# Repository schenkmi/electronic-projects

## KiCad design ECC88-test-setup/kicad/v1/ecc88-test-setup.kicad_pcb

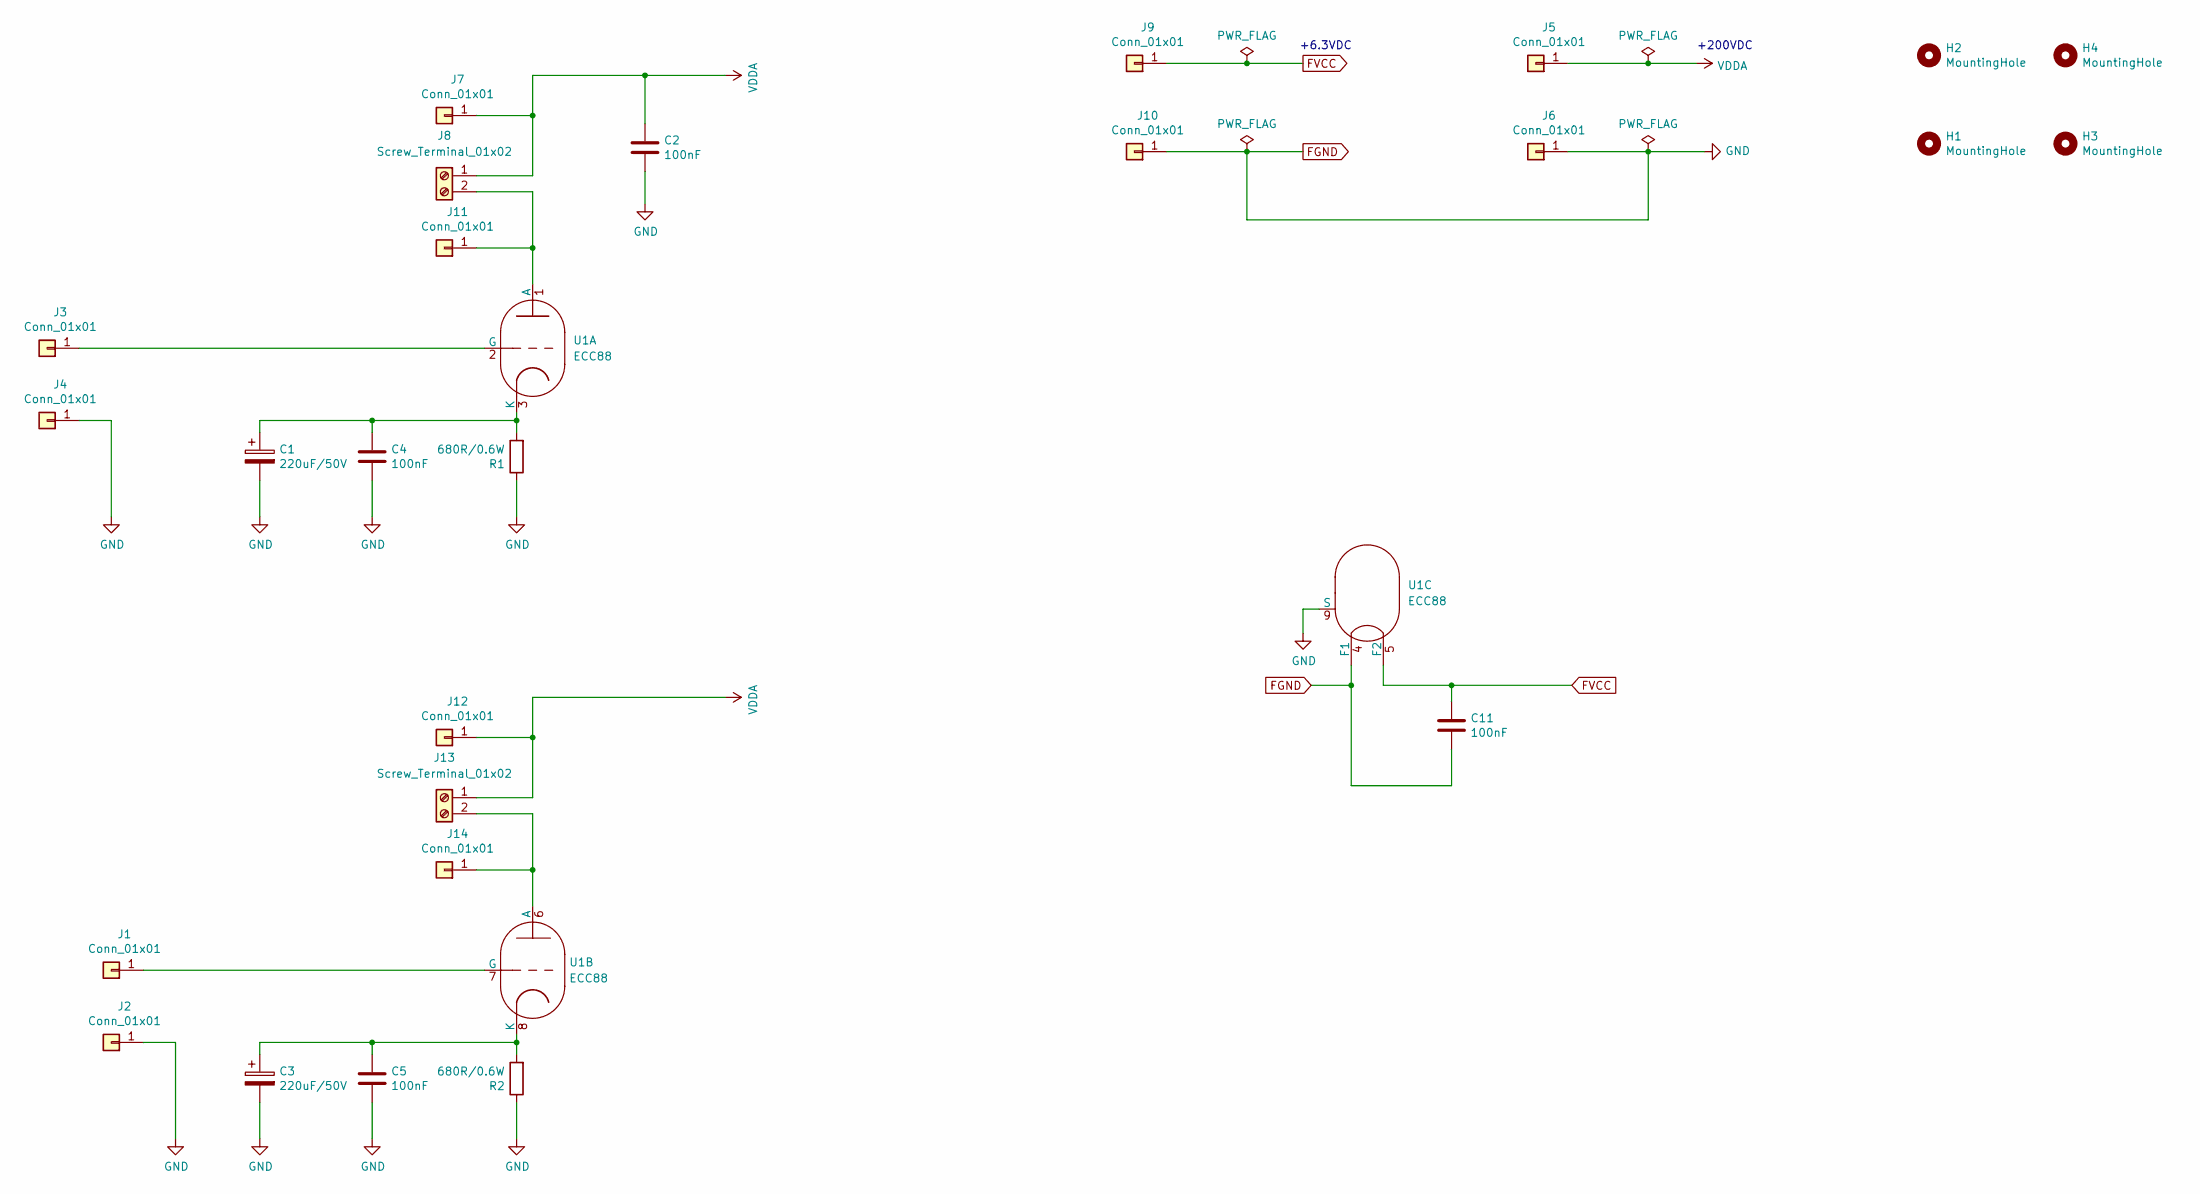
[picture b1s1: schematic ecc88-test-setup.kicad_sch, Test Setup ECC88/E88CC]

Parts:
C1, C3: 220uF/50V; CP_Radial_D8.0mm_P3.50mm
C2: 100nF; C_Rect_L16.5mm_W5.0mm_P15.00mm_MKT
C4, C5, C11: 100nF; C_Rect_L7.2mm_W2.5mm_P5.00mm_FKS2_FKP2_MKS2_MKP2
H1, H2, H3, H4: MountingHole; MountingHole_3.2mm_M3
J1, J2, J3, J4, J7, J11, J12, J14: Conn_01x01; Pin_D1.0mm_L10.0mm
J5, J6, J9, J10: Conn_01x01; Pin_D1.3mm_L11.0mm
J8, J13: Screw_Terminal_01x02; TerminalBlock_RND_205-00012_1x02_P5.00mm_Horizontal
R1, R2: 680R/0.6W; R_Axial_DIN0207_L6.3mm_D2.5mm_P10.16mm_Horizontal
U1: ECC88; socket_gzc9-b

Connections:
FGND: C1.2, C2.2, C3.2, C4.2, C5.2, C11.2, J2.1, J4.1, J6.1, J10.1, R1.1, R2.1, U1.4 (F1), U1.9 (S)
FVCC: C11.1, J9.1, U1.5 (F2)
unnamed: C3.1, C5.1, R2.2, U1.8 (K)
unnamed: J1.1, U1.7 (G)
unnamed: J3.1, U1.2 (G)
unnamed: J13.2, J14.1, U1.6 (A)
unnamed: J8.2, J11.1, U1.1 (A)
unnamed: C1.1, C4.1, R1.2, U1.3 (K)
VDDA: C2.1, J5.1, J7.1, J8.1, J12.1, J13.1

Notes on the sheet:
+6.3VDC
+200VDC

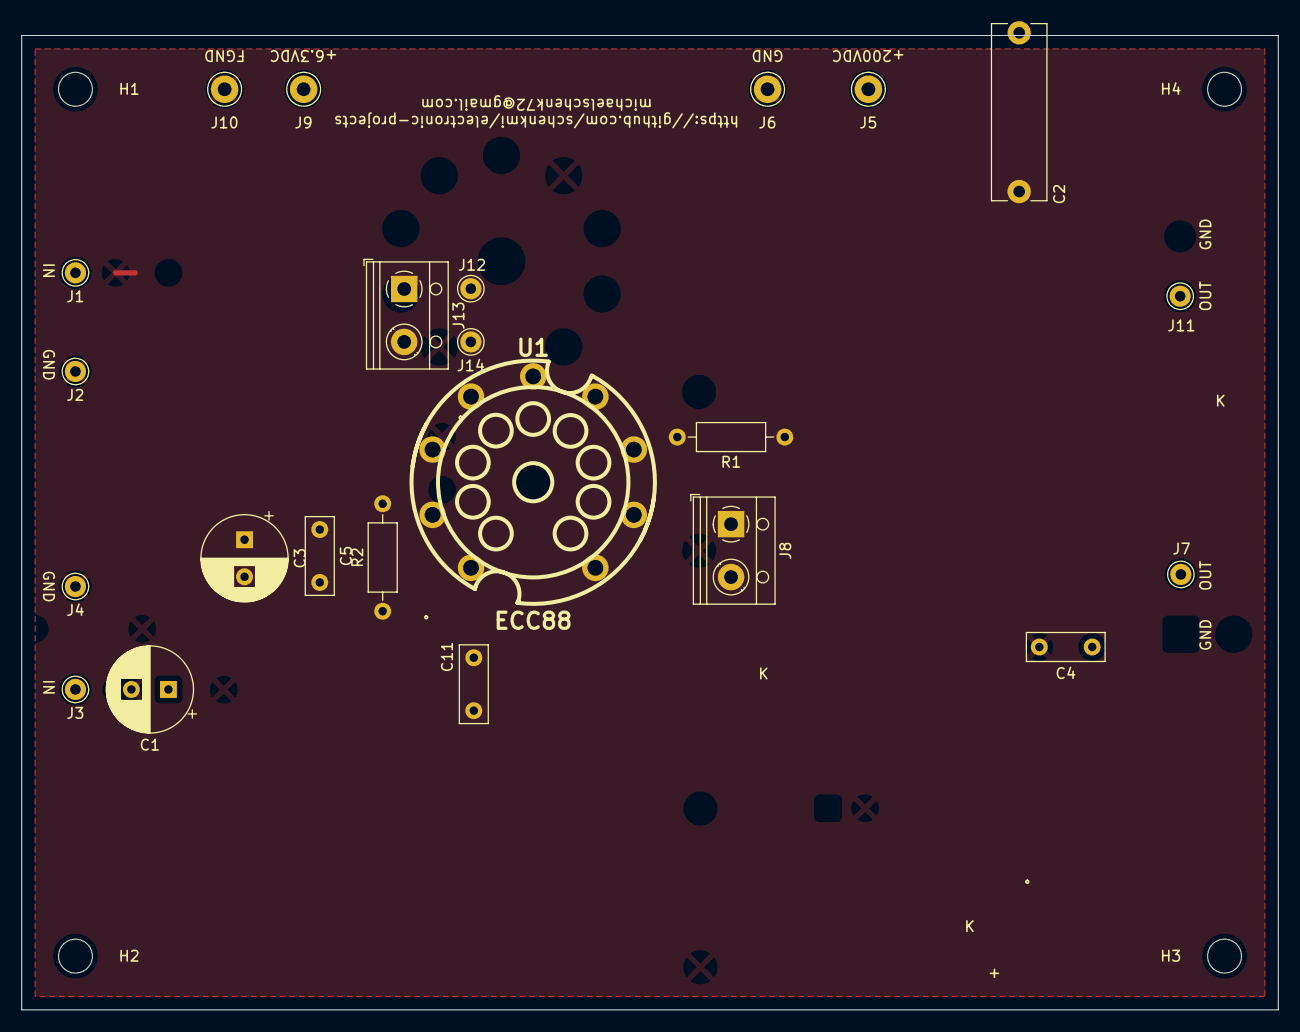
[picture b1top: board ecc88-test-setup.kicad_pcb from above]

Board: 2 copper layers, 118.7 x 92.1 mm, 27 parts (0 on the bottom side), 9 nets.

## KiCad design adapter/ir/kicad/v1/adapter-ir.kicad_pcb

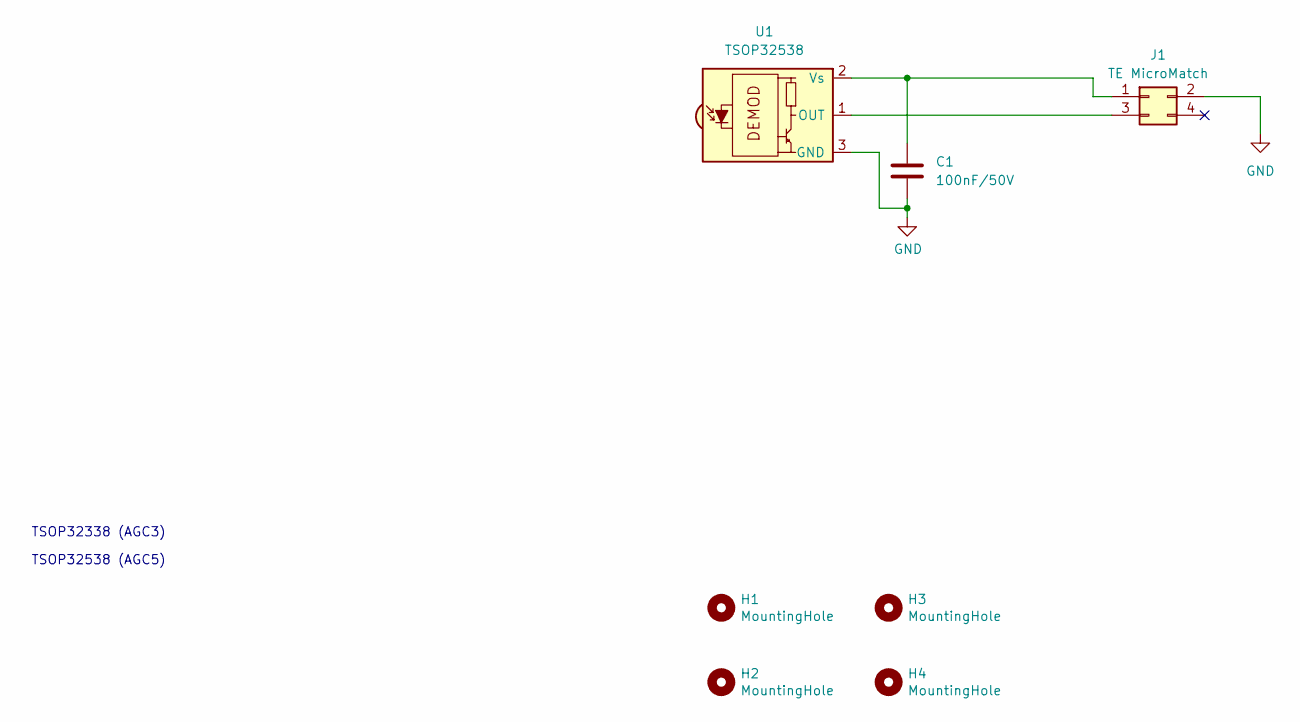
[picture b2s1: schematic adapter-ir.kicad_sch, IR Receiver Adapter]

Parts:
C1: 100nF/50V; C_0805_2012Metric_Pad1.18x1.45mm_HandSolder
H1, H2, H3, H4: MountingHole; MountingHole_3.2mm_M3_Pad_Via
J1: TE MicroMatch; TE_Micro-MaTch_215079-4_2x02_P1.27mm_Vertical
U1: TSOP32538; Vishay_MOLD-3Pin

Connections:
GND: C1.2, J1.2, U1.3 (GND)
unnamed: C1.1, J1.1, U1.2 (Vs)
unnamed: J1.3, U1.1 (OUT)

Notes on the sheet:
TSOP32338 (AGC3)
TSOP32538 (AGC5)

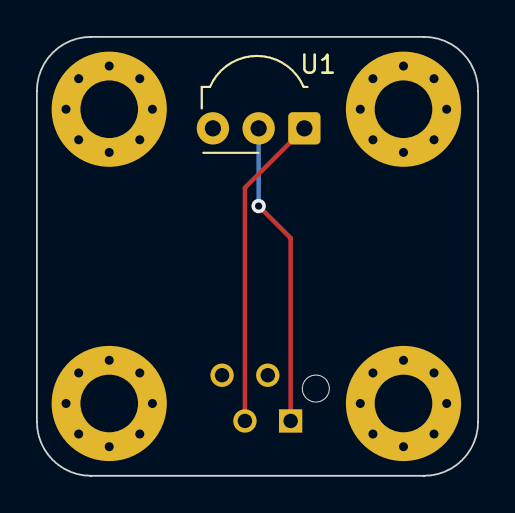
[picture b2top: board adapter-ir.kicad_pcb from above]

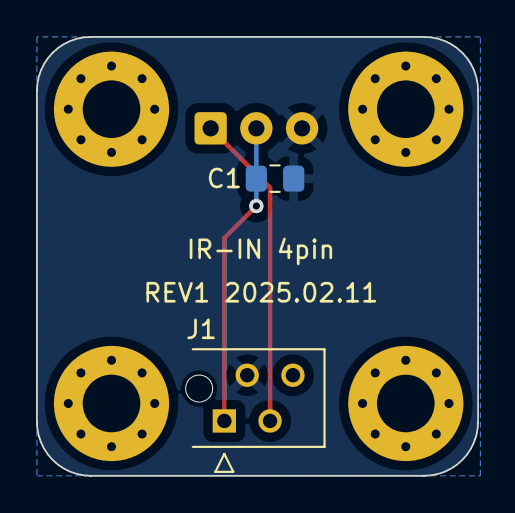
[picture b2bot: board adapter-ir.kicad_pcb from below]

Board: 2 copper layers, 24.5 x 24.4 mm, 7 parts (2 on the bottom side), 3 nets.

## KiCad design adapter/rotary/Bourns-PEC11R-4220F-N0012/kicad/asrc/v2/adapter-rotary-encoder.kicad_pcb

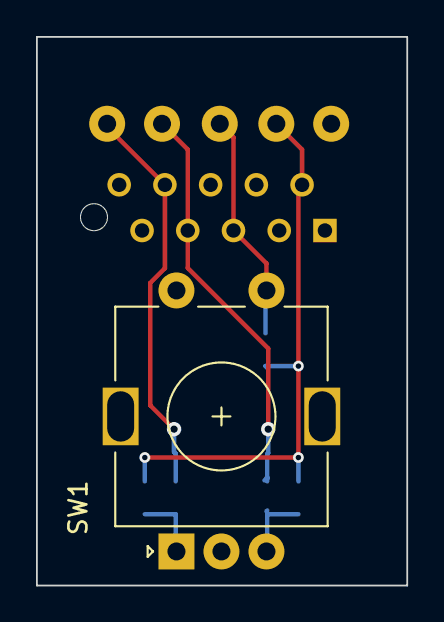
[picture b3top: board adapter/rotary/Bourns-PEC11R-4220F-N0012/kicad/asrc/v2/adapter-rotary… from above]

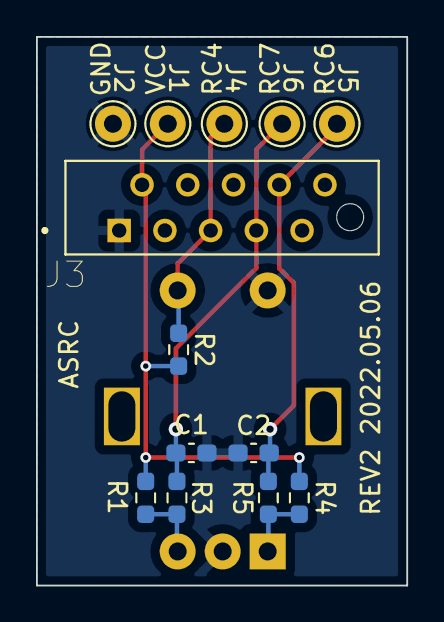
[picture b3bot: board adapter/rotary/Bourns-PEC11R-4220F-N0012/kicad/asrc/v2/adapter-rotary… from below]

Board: 2 copper layers, 20.6 x 30.5 mm, 14 parts (13 on the bottom side), 7 nets.

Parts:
C1, C2: 10nF; C_0603_1608Metric_Pad1.08x0.95mm_HandSolder
J1: VCC; Pin_D1.0mm_L10.0mm
J2: GND; Pin_D1.0mm_L10.0mm
J3: B; TE_CONN_RCPT_10POS_0.1_TIN_PCB
J4: RC4; Pin_D1.0mm_L10.0mm
J5: RC6; Pin_D1.0mm_L10.0mm
J6: RC7; Pin_D1.0mm_L10.0mm
R1, R2, R3, R4, R5: 10k; R_0603_1608Metric_Pad0.98x0.95mm_HandSolder
SW1: RotaryEncoder_Switch; RotaryEncoder_Alps_EC11E-Switch_Vertical_H20mm

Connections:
GND: C1.1, C2.1, J2.1, J3.1, SW1.C, SW1.S2
unnamed: R1.2, R3.1, SW1.B
unnamed: R4.2, R5.1, SW1.A
RC4/SW: J3.5, J4.1, R2.1, SW1.S1
RC6/CHA: C2.2, J3.8, J5.1, R5.2
RC7/CHB: C1.2, J3.7, J6.1, R3.2
VCC: J1.1, J3.2, R1.1, R2.2, R4.1

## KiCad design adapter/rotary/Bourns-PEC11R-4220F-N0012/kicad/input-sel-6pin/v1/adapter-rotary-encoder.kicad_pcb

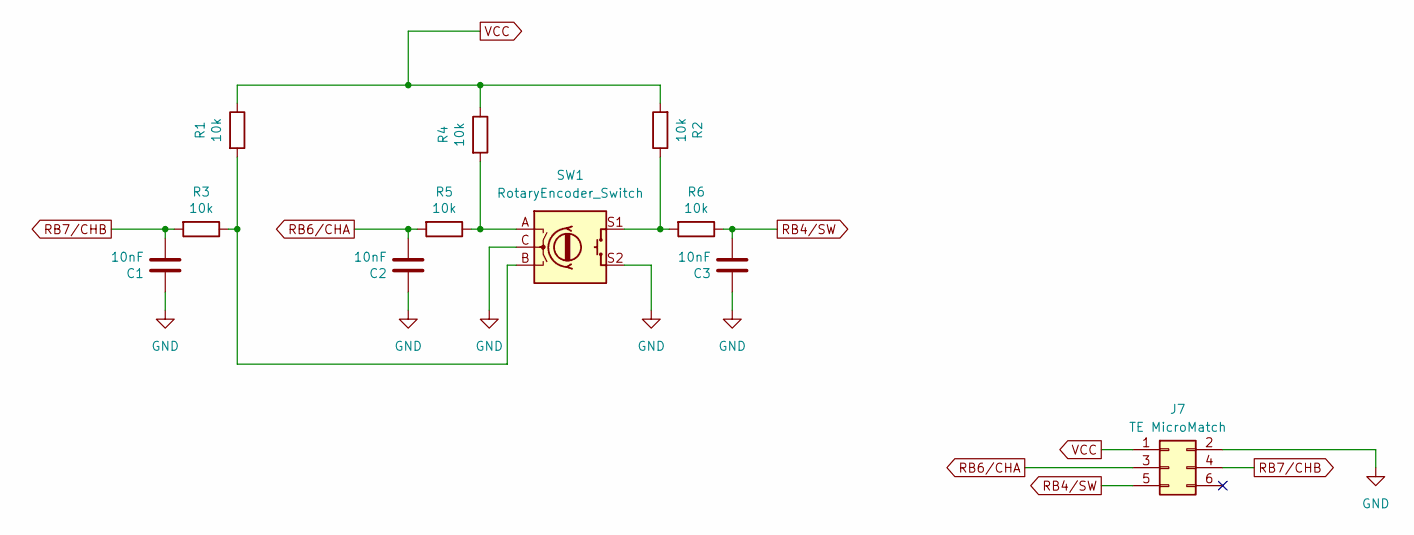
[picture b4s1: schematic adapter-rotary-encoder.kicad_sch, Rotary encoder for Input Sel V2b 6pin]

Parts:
C1, C2, C3: 10nF; C_0603_1608Metric_Pad1.08x0.95mm_HandSolder
J7: TE MicroMatch; TE_Micro-MaTch_215079-6_2x03_P1.27mm_Vertical
R1, R2, R3, R4, R5, R6: 10k; R_0603_1608Metric_Pad0.98x0.95mm_HandSolder
SW1: RotaryEncoder_Switch; RotaryEncoder_Alps_EC11E-Switch_Vertical_H20mm

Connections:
GND: C1.1, C2.1, C3.1, J7.2, SW1.C, SW1.S2
unnamed: R1.2, R3.1, SW1.B
unnamed: R2.1, R6.2, SW1.S1
unnamed: R4.2, R5.1, SW1.A
RB4/SW: C3.2, J7.5, R6.1
RB6/CHA: C2.2, J7.3, R5.2
RB7/CHB: C1.2, J7.4, R3.2
VCC: J7.1, R1.1, R2.2, R4.1

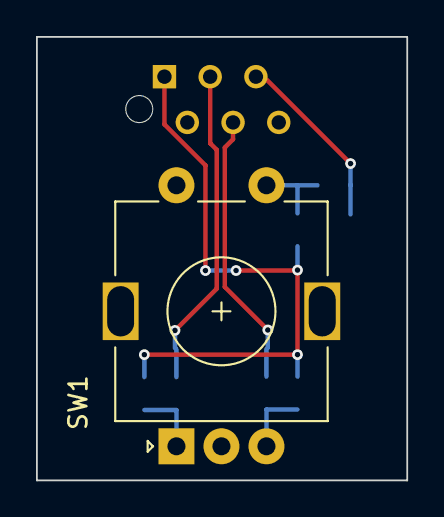
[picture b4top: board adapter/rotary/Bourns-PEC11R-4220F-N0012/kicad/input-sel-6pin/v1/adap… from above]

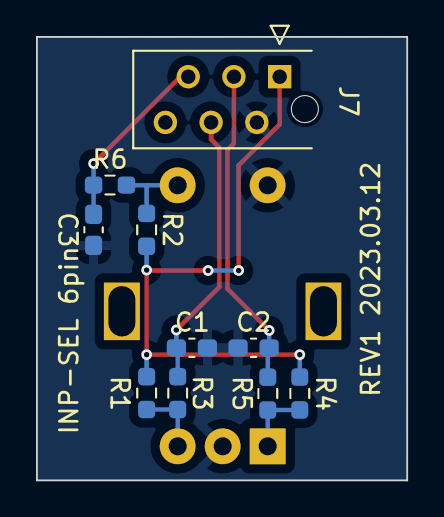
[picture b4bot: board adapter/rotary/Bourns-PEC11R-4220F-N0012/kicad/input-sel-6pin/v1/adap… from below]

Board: 2 copper layers, 20.6 x 24.6 mm, 11 parts (10 on the bottom side), 8 nets.

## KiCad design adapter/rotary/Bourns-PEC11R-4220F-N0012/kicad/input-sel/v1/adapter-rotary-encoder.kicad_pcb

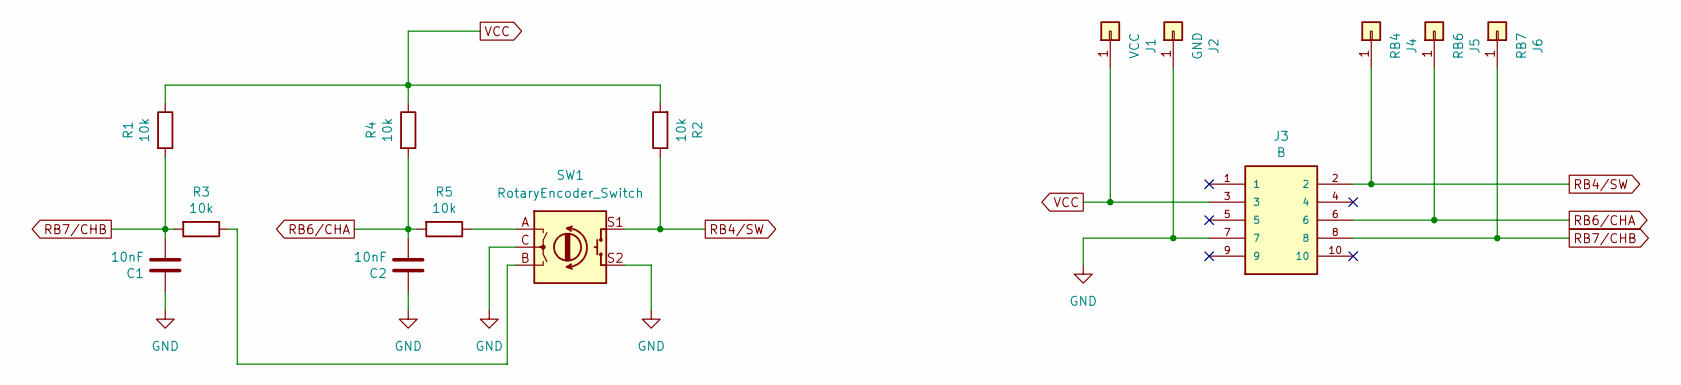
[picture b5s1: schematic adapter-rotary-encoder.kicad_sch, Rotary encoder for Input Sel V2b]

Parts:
C1, C2: 10nF; C_0603_1608Metric_Pad1.08x0.95mm_HandSolder
J1: VCC; Pin_D1.0mm_L10.0mm
J2: GND; Pin_D1.0mm_L10.0mm
J3: B; TE_CONN_RCPT_10POS_0.1_TIN_PCB
J4: RB4; Pin_D1.0mm_L10.0mm
J5: RB6; Pin_D1.0mm_L10.0mm
J6: RB7; Pin_D1.0mm_L10.0mm
R1, R2, R3, R4, R5: 10k; R_0603_1608Metric_Pad0.98x0.95mm_HandSolder
SW1: RotaryEncoder_Switch; RotaryEncoder_Alps_EC11E-Switch_Vertical_H20mm

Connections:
GND: C1.1, C2.1, J2.1, J3.7, SW1.C, SW1.S2
unnamed: R3.1, SW1.B
unnamed: R5.1, SW1.A
RB4/SW: J3.2, J4.1, R2.1, SW1.S1
RB6/CHA: C2.2, J3.6, J5.1, R4.2, R5.2
RB7/CHB: C1.2, J3.8, J6.1, R1.2, R3.2
VCC: J1.1, J3.3, R1.1, R2.2, R4.1

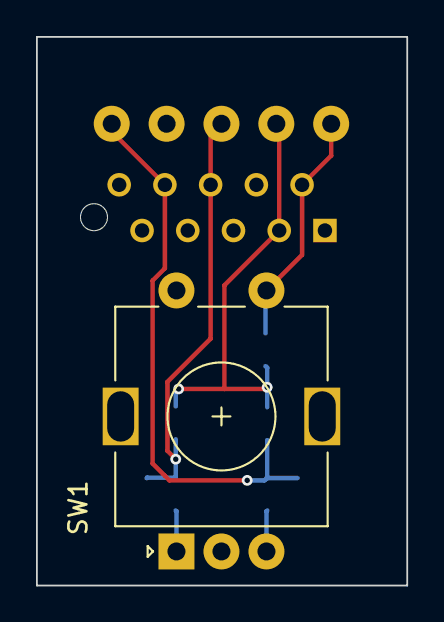
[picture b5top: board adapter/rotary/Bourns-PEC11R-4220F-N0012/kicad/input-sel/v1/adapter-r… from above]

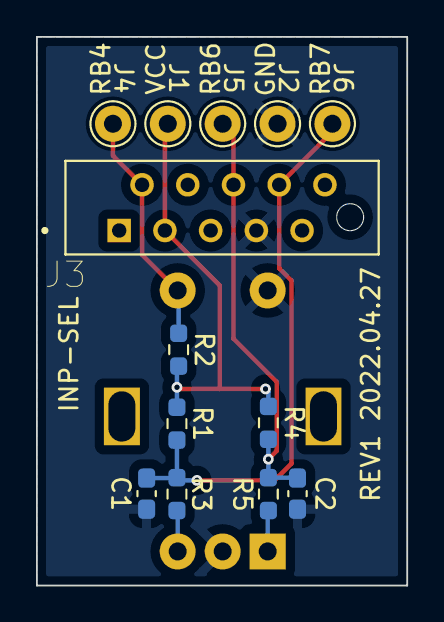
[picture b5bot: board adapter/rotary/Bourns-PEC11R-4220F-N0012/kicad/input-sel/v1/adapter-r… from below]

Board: 2 copper layers, 20.6 x 30.5 mm, 14 parts (13 on the bottom side), 7 nets.
